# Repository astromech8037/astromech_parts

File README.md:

# Astromech Parts

This is my collection of astromechs.  
For more details on these parts, as well blueprints and general information on how to build a astromech droid, please visit https://astromech.net  

The GitHub repository will be split into the following areas:

3D Files:  This area will contain all 3D files I have created.  Each piece will have a readme with the best way to produce the file (ie:  3D printing, CNC, etc)

Electronics:  This area will contain all the electronics I have created.   In addition, any code for running the electronics will be here.

Happy building!

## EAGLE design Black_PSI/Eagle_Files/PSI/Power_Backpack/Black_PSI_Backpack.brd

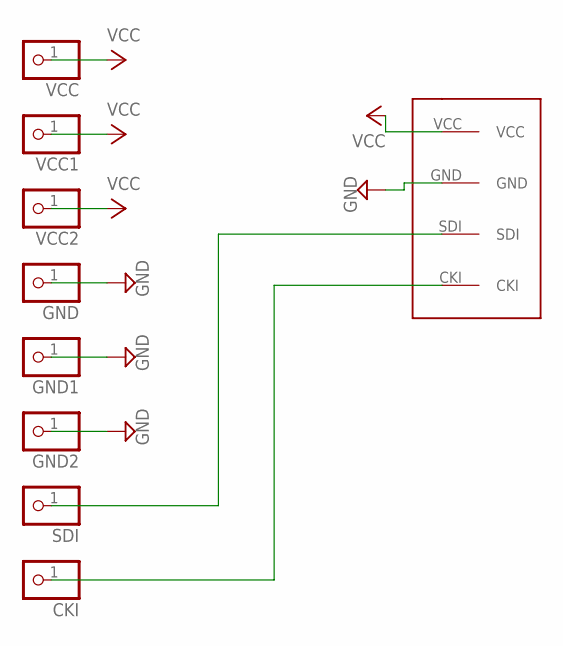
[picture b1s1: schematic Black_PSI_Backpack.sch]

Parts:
CKI: PINHD-1X1; 1X01
GND, GND1, GND2: PINHD-1X1; 1X01
SDI: PINHD-1X1; 1X01
U$1: 0393570004WIRE-TO-BOARD
VCC, VCC1, VCC2: PINHD-1X1; 1X01

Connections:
CKI: CKI.1, U$1.CKI
GND: GND.1, GND1.1, GND2.1, U$1.GND
SDI: SDI.1, U$1.SDI
VCC: U$1.VCC, VCC.1, VCC1.1, VCC2.1

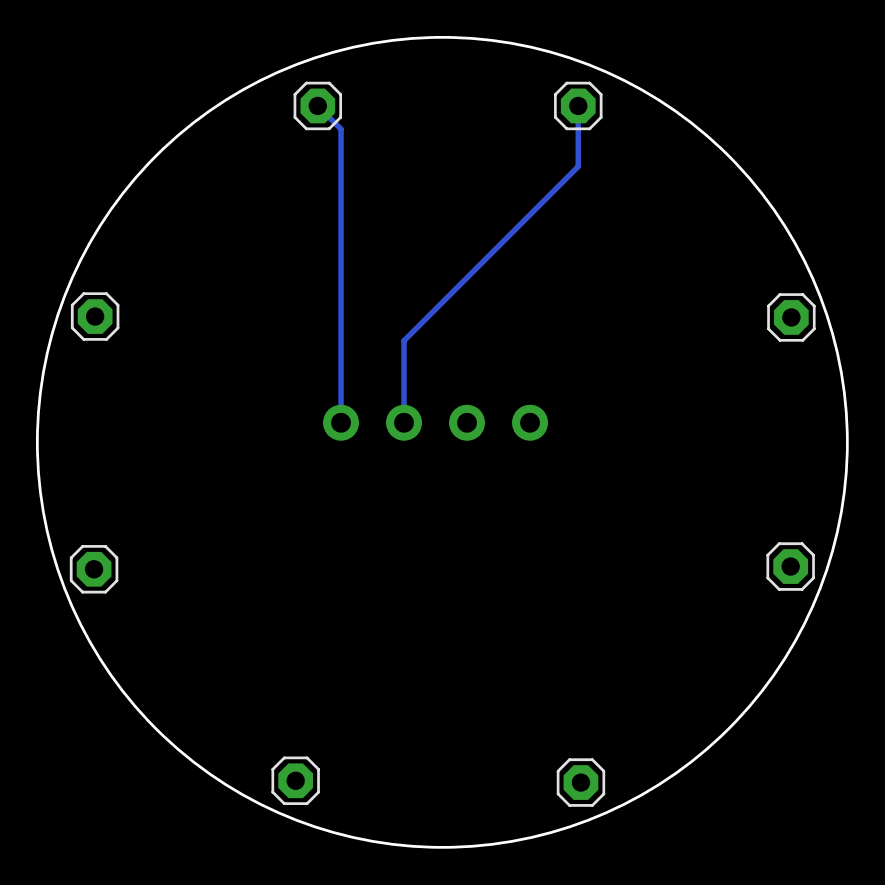
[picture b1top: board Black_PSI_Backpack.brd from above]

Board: 2 copper layers, 45.0 x 45.0 mm, 9 parts (1 on the bottom side), 4 nets.

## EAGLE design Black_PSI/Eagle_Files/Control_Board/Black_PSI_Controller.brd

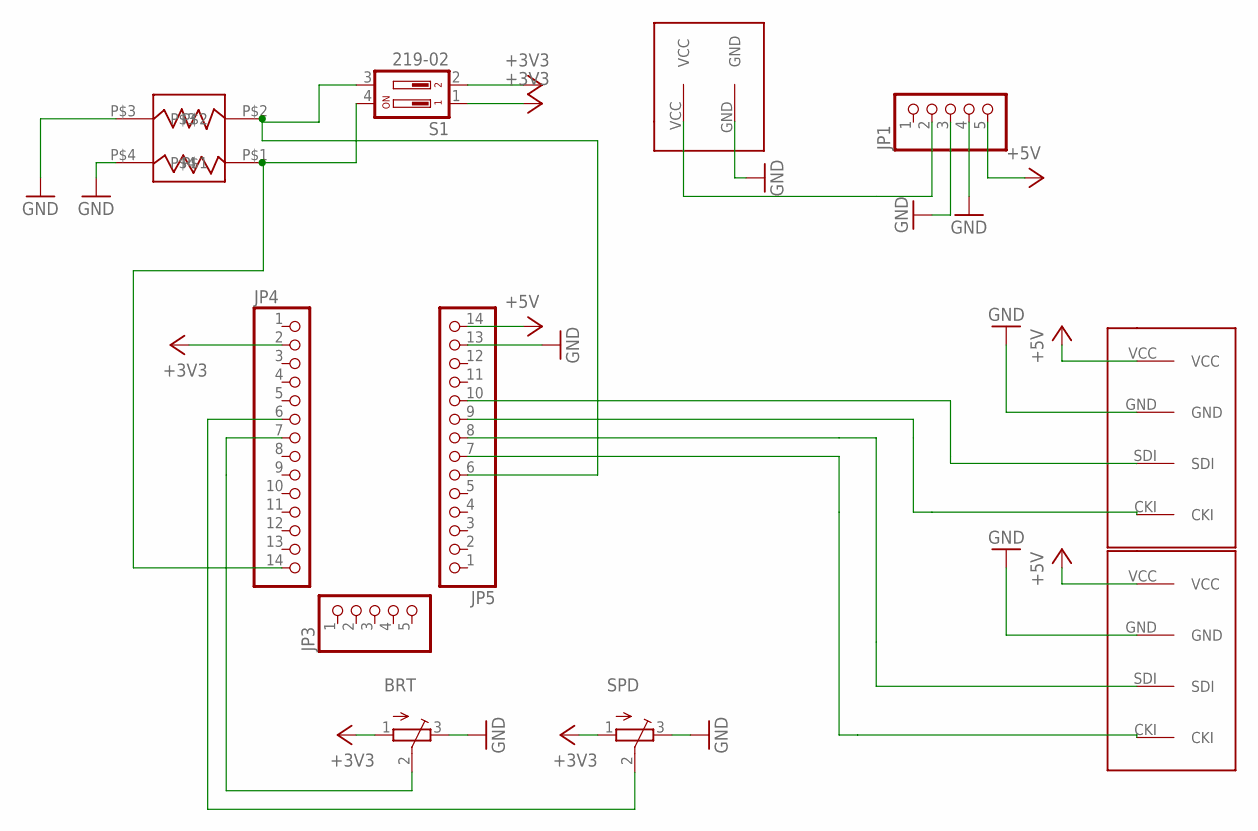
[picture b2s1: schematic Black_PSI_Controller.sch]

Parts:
BRT: TRIMPOTTC33X; TC33X
JP1, JP3: PINHD-1X5; 1X05
JP4, JP5: PINHD-1X14; 1X14
S1: 219-02; CTS-219-02
SPD: TRIMPOTTC33X; TC33X
U$1: 0393570002WIRE-TO-BOARD
U$2, U$3: 0393570004WIRE-TO-BOARD
U$4: ACASN1002S1002P1AT

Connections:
+3V3: BRT.1 (A), JP4.2, S1.1, S1.2, SPD.1 (A)
+5V: JP1.5, JP5.14, U$2.VCC, U$3.VCC
GND: BRT.3 (E), JP1.3, JP1.4, JP5.13, SPD.3 (E), U$1.GND, U$2.GND, U$3.GND, U$4.P$3, U$4.P$4
unnamed: JP4.6, SPD.2 (S)
unnamed: BRT.2 (S), JP4.7
unnamed: JP1.2, U$1.VCC
unnamed: JP5.10, U$2.SDI
unnamed: JP5.9, U$2.CKI
unnamed: JP5.8, U$3.SDI
unnamed: JP5.7, U$3.CKI
unnamed: JP4.14, S1.4, U$4.P$1
unnamed: JP5.6, S1.3, U$4.P$2

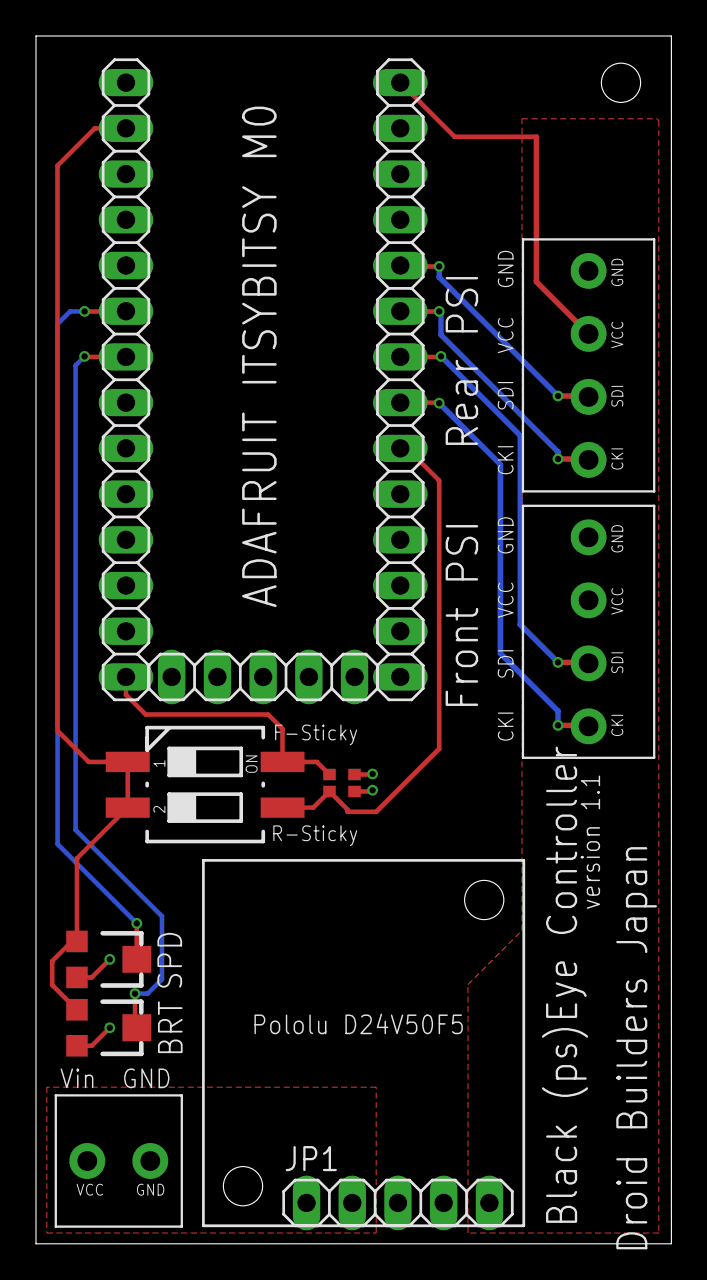
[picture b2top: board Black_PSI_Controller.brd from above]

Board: 2 copper layers, 35.3 x 67.1 mm, 11 parts (0 on the bottom side), 12 nets.

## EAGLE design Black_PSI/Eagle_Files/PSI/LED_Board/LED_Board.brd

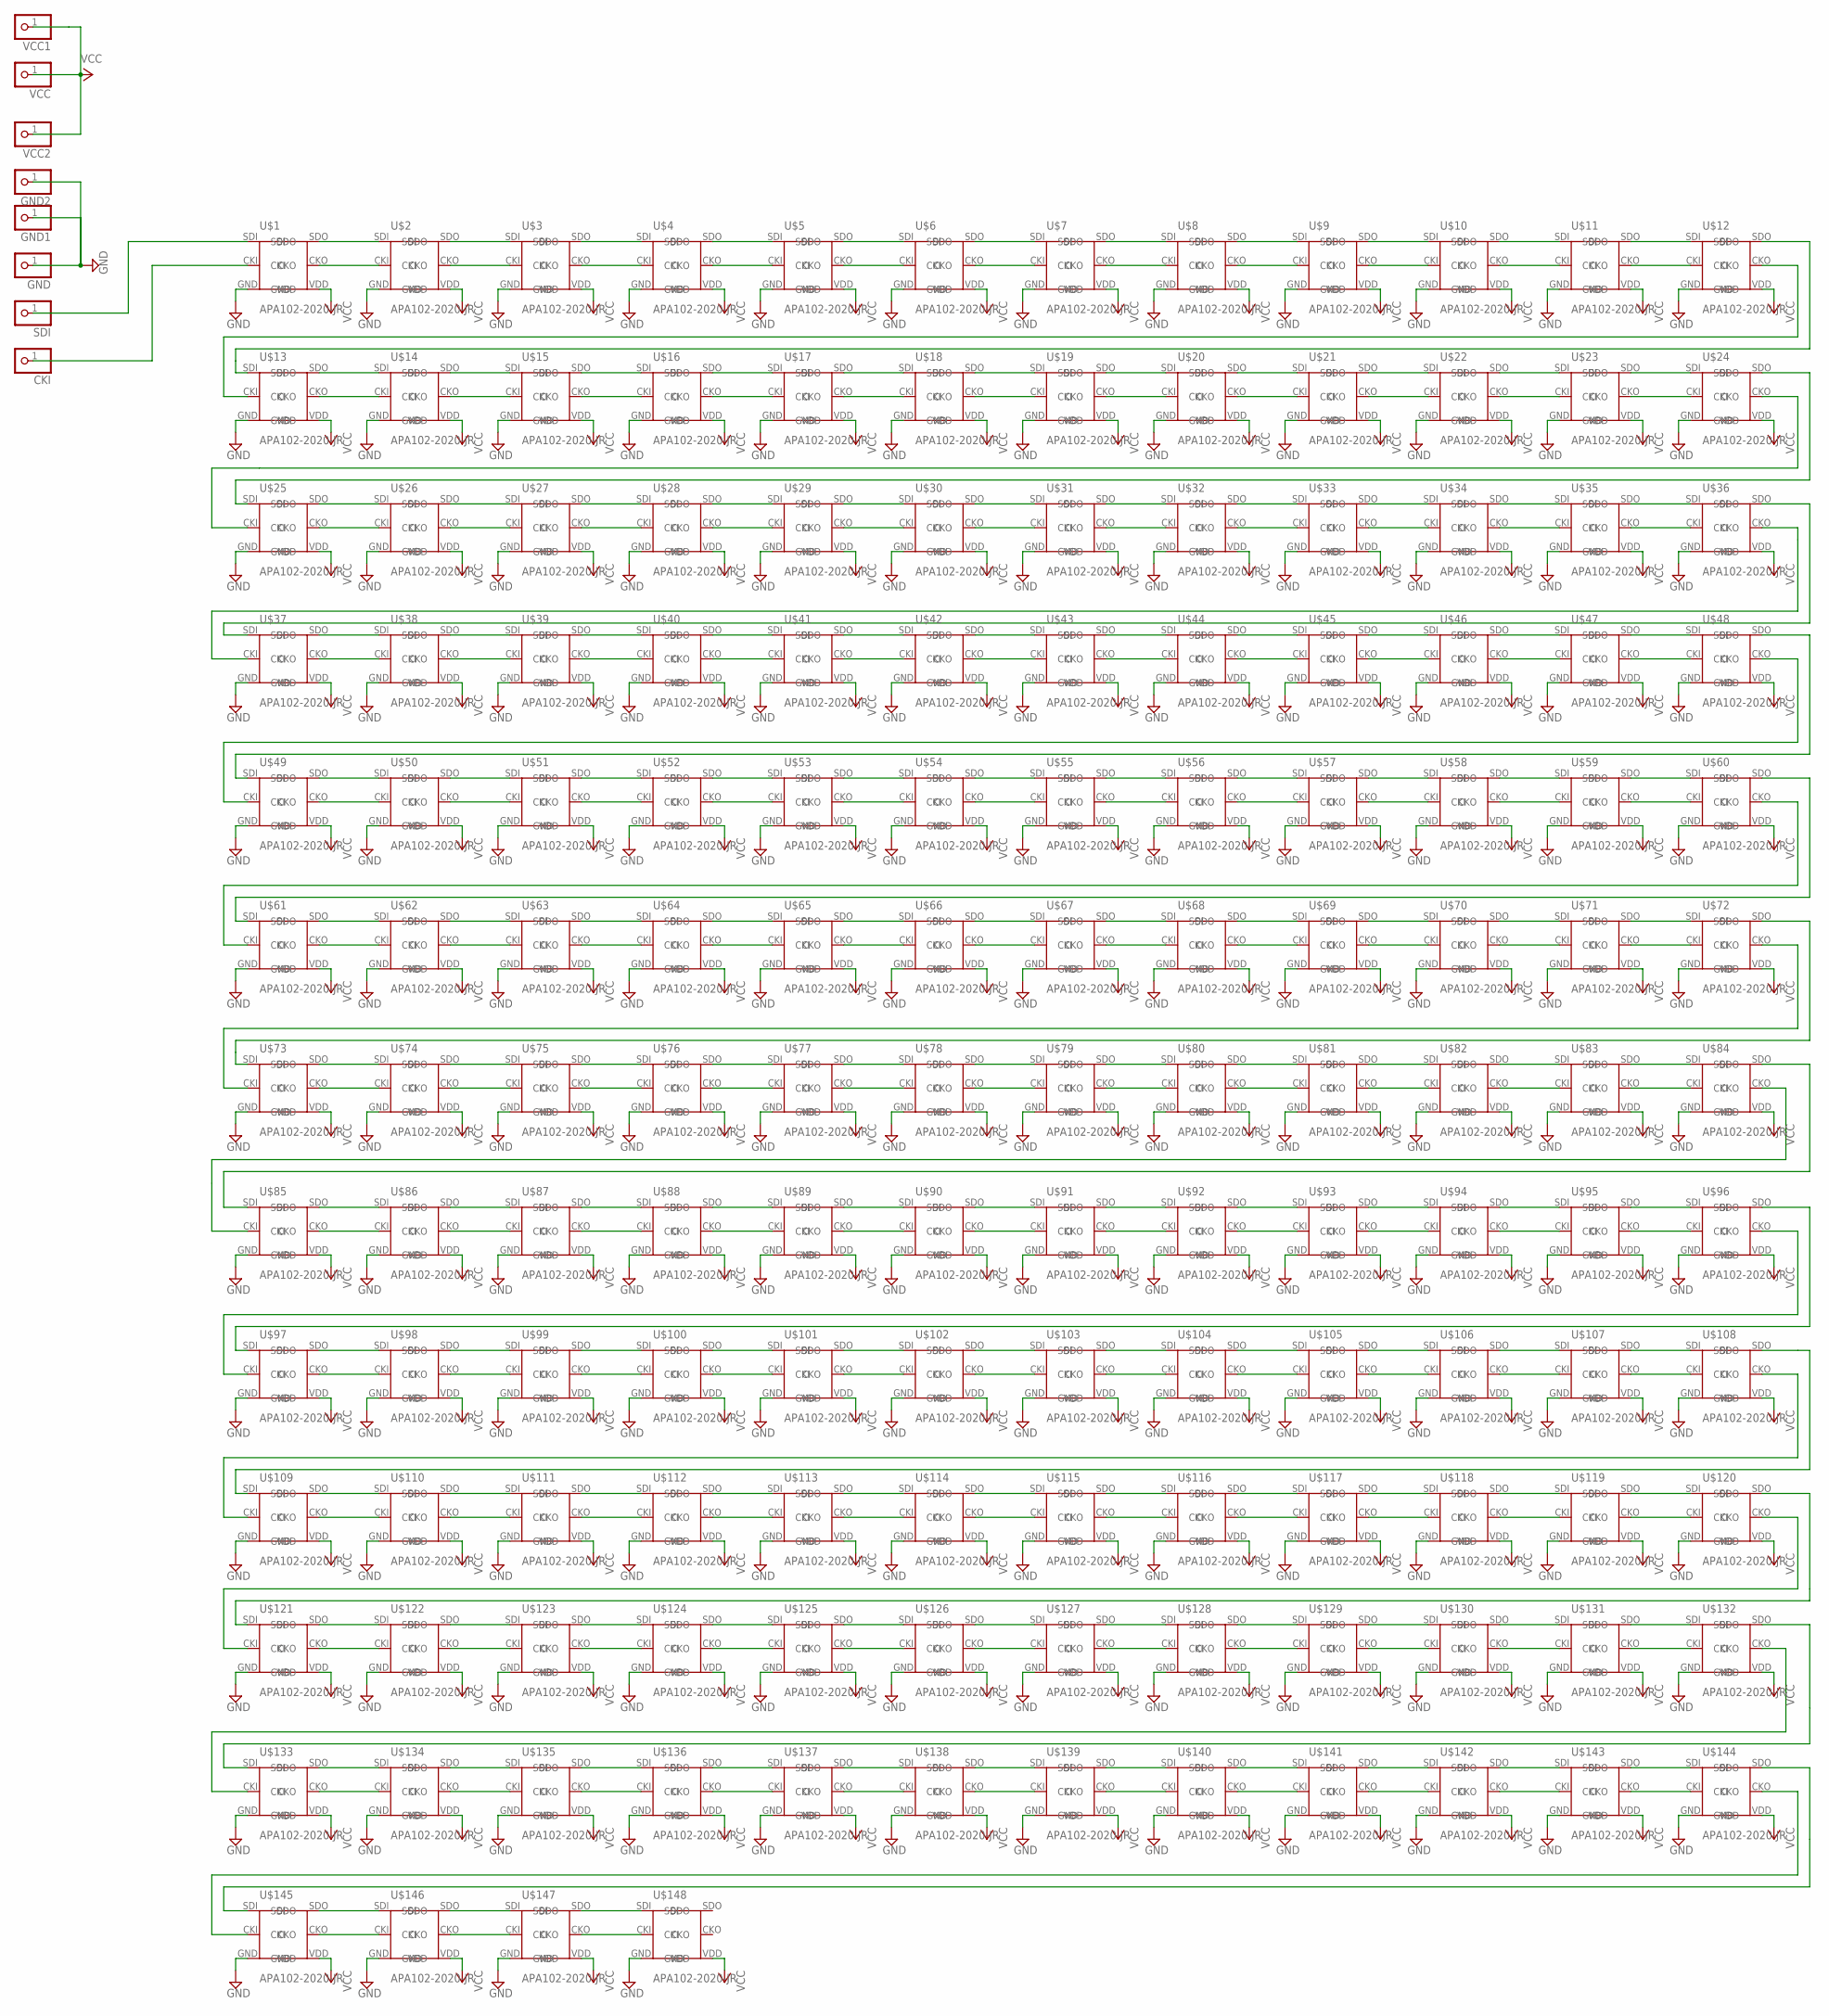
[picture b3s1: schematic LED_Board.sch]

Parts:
CKI: PINHD-1X1; 1X01
GND, GND1, GND2: PINHD-1X1; 1X01
SDI: PINHD-1X1; 1X01
U$1, U$2, U$3, U$4, U$5, U$6, U$7, U$8, U$9, U$10, U$11, U$12, U$13, U$14, U$15, U$16, U$17, U$18, U$19, U$20, U$21, U$22, U$23, U$24, U$25, U$26, U$27, U$28, U$29, U$30, U$31, U$32, U$33, U$34, U$35, U$36, U$37, U$38, U$39, U$40, U$41, U$42, U$43, U$44, U$45, U$46, U$47, U$48, U$49, U$50, U$51, U$52, U$53, U$54, U$55, U$56, U$57, U$58, U$59, U$60, U$61, U$62, U$63, U$64, U$65, U$66, U$67, U$68, U$69, U$70, U$71, U$72, U$73, U$74, U$75, U$76, U$77, U$78, U$79, U$80, U$81, U$82, U$83, U$84, U$85, U$86, U$87, U$88, U$89, U$90, U$91, U$92, U$93, U$94, U$95, U$96, U$97, U$98, U$99, U$100, U$101, U$102, U$103, U$104, U$105, U$106, U$107, U$108, U$109, U$110, U$111, U$112, U$113, U$114, U$115, U$116, U$117, U$118, U$119, U$120, U$121, U$122, U$123, U$124, U$125, U$126, U$127, U$128, U$129, U$130, U$131, U$132, U$133, U$134, U$135, U$136, U$137, U$138, U$139, U$140, U$141, U$142, U$143, U$144, U$145, U$146, U$147, U$148: APA102-2020-JR
VCC, VCC1, VCC2: PINHD-1X1; 1X01

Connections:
CK-01: U$4.CKO, U$5.CKI
CK-02: U$12.CKO, U$13.CKI
CK-03: U$22.CKO, U$23.CKI
CK-04: U$34.CKO, U$35.CKI
CK-05: U$46.CKO, U$47.CKI
CK-06: U$60.CKO, U$61.CKI
CK-07: U$74.CKO, U$75.CKI
CK-08: U$88.CKO, U$89.CKI
CK-09: U$102.CKO, U$103.CKI
CK-10: U$114.CKO, U$115.CKI
CK-11: U$126.CKO, U$127.CKI
CK-12: U$136.CKO, U$137.CKI
CK-13: U$144.CKO, U$145.CKI
GND: GND.1, GND1.1, GND2.1, U$1.GND, U$2.GND, U$3.GND, U$4.GND, U$5.GND, U$6.GND, U$7.GND, U$8.GND, U$9.GND, U$10.GND, U$11.GND, U$12.GND, U$13.GND, U$14.GND, U$15.GND, U$16.GND, U$17.GND, U$18.GND, U$19.GND, U$20.GND, U$21.GND, U$22.GND, U$23.GND, U$24.GND, U$25.GND, U$26.GND, U$27.GND, U$28.GND, U$29.GND, U$30.GND, U$31.GND, U$32.GND, U$33.GND, U$34.GND, U$35.GND, U$36.GND, U$37.GND, U$38.GND, U$39.GND, U$40.GND, U$41.GND, U$42.GND, U$43.GND, U$44.GND, U$45.GND, U$46.GND, U$47.GND, U$48.GND, U$49.GND, U$50.GND, U$51.GND, U$52.GND, U$53.GND, U$54.GND, U$55.GND, U$56.GND, U$57.GND, U$58.GND, U$59.GND, U$60.GND, U$61.GND, U$62.GND, U$63.GND, U$64.GND, U$65.GND, U$66.GND, U$67.GND, U$68.GND, U$69.GND, U$70.GND, U$71.GND, U$72.GND, U$73.GND, U$74.GND, U$75.GND, U$76.GND, U$77.GND, U$78.GND, U$79.GND, U$80.GND, U$81.GND, U$82.GND, U$83.GND, U$84.GND, U$85.GND, U$86.GND, U$87.GND, U$88.GND, U$89.GND, U$90.GND, U$91.GND, U$92.GND, U$93.GND, U$94.GND, U$95.GND, U$96.GND, U$97.GND, U$98.GND, U$99.GND, U$100.GND, U$101.GND, U$102.GND, U$103.GND, U$104.GND, U$105.GND, U$106.GND, U$107.GND, U$108.GND, U$109.GND, U$110.GND, U$111.GND, U$112.GND, U$113.GND, U$114.GND, U$115.GND, U$116.GND, U$117.GND, U$118.GND, U$119.GND, U$120.GND, U$121.GND, U$122.GND, U$123.GND, U$124.GND, U$125.GND, U$126.GND, U$127.GND, U$128.GND, U$129.GND, U$130.GND, U$131.GND, U$132.GND, U$133.GND, U$134.GND, U$135.GND, U$136.GND, U$137.GND, U$138.GND, U$139.GND, U$140.GND, U$141.GND, U$142.GND, U$143.GND, U$144.GND, U$145.GND, U$146.GND, U$147.GND, U$148.GND
unnamed: SDI.1, U$1.SDI
unnamed: CKI.1, U$1.CKI
unnamed: U$11.CKO, U$12.CKI
unnamed: U$11.SDO, U$12.SDI
unnamed: U$10.CKO, U$11.CKI
unnamed: U$10.SDO, U$11.SDI
unnamed: U$9.SDO, U$10.SDI
unnamed: U$9.CKO, U$10.CKI
unnamed: U$8.SDO, U$9.SDI
unnamed: U$8.CKO, U$9.CKI
unnamed: U$7.SDO, U$8.SDI
unnamed: U$7.CKO, U$8.CKI
unnamed: U$6.SDO, U$7.SDI
unnamed: U$6.CKO, U$7.CKI
unnamed: U$5.SDO, U$6.SDI
unnamed: U$5.CKO, U$6.CKI
unnamed: U$3.SDO, U$4.SDI
unnamed: U$3.CKO, U$4.CKI
unnamed: U$2.SDO, U$3.SDI
unnamed: U$2.CKO, U$3.CKI
unnamed: U$1.SDO, U$2.SDI
unnamed: U$1.CKO, U$2.CKI
unnamed: U$23.CKO, U$24.CKI
unnamed: U$23.SDO, U$24.SDI
unnamed: U$21.SDO, U$22.SDI
unnamed: U$21.CKO, U$22.CKI
unnamed: U$20.SDO, U$21.SDI
unnamed: U$20.CKO, U$21.CKI
unnamed: U$19.SDO, U$20.SDI
unnamed: U$19.CKO, U$20.CKI
unnamed: U$18.SDO, U$19.SDI
unnamed: U$18.CKO, U$19.CKI
unnamed: U$17.SDO, U$18.SDI
unnamed: U$17.CKO, U$18.CKI
unnamed: U$16.SDO, U$17.SDI
unnamed: U$16.CKO, U$17.CKI
unnamed: U$15.SDO, U$16.SDI
unnamed: U$15.CKO, U$16.CKI
unnamed: U$14.SDO, U$15.SDI
unnamed: U$14.CKO, U$15.CKI
unnamed: U$13.SDO, U$14.SDI
unnamed: U$13.CKO, U$14.CKI
unnamed: U$35.CKO, U$36.CKI
unnamed: U$35.SDO, U$36.SDI
unnamed: U$33.SDO, U$34.SDI
unnamed: U$33.CKO, U$34.CKI
unnamed: U$32.SDO, U$33.SDI
unnamed: U$32.CKO, U$33.CKI
unnamed: U$31.SDO, U$32.SDI
unnamed: U$31.CKO, U$32.CKI
unnamed: U$30.SDO, U$31.SDI
unnamed: U$30.CKO, U$31.CKI
unnamed: U$29.SDO, U$30.SDI
unnamed: U$29.CKO, U$30.CKI
unnamed: U$28.SDO, U$29.SDI
unnamed: U$28.CKO, U$29.CKI
unnamed: U$27.SDO, U$28.SDI
unnamed: U$27.CKO, U$28.CKI
unnamed: U$26.SDO, U$27.SDI
unnamed: U$26.CKO, U$27.CKI
unnamed: U$25.SDO, U$26.SDI
unnamed: U$25.CKO, U$26.CKI
unnamed: U$47.CKO, U$48.CKI
unnamed: U$47.SDO, U$48.SDI
unnamed: U$45.SDO, U$46.SDI
unnamed: U$45.CKO, U$46.CKI
unnamed: U$44.SDO, U$45.SDI
unnamed: U$44.CKO, U$45.CKI
unnamed: U$43.SDO, U$44.SDI
unnamed: U$43.CKO, U$44.CKI
unnamed: U$42.SDO, U$43.SDI
unnamed: U$42.CKO, U$43.CKI
unnamed: U$41.SDO, U$42.SDI
unnamed: U$41.CKO, U$42.CKI
unnamed: U$40.SDO, U$41.SDI
unnamed: U$40.CKO, U$41.CKI
unnamed: U$39.SDO, U$40.SDI
unnamed: U$39.CKO, U$40.CKI
unnamed: U$38.SDO, U$39.SDI
unnamed: U$38.CKO, U$39.CKI
unnamed: U$37.SDO, U$38.SDI
unnamed: U$37.CKO, U$38.CKI
unnamed: U$59.CKO, U$60.CKI
unnamed: U$59.SDO, U$60.SDI
unnamed: U$58.CKO, U$59.CKI
unnamed: U$58.SDO, U$59.SDI
unnamed: U$57.SDO, U$58.SDI
unnamed: U$57.CKO, U$58.CKI
unnamed: U$56.SDO, U$57.SDI
unnamed: U$56.CKO, U$57.CKI
unnamed: U$55.SDO, U$56.SDI
unnamed: U$55.CKO, U$56.CKI
unnamed: U$54.SDO, U$55.SDI
unnamed: U$54.CKO, U$55.CKI
unnamed: U$53.SDO, U$54.SDI
unnamed: U$53.CKO, U$54.CKI
unnamed: U$52.SDO, U$53.SDI
unnamed: U$52.CKO, U$53.CKI
unnamed: U$51.SDO, U$52.SDI
unnamed: U$51.CKO, U$52.CKI
unnamed: U$50.SDO, U$51.SDI
unnamed: U$50.CKO, U$51.CKI
unnamed: U$49.SDO, U$50.SDI
unnamed: U$49.CKO, U$50.CKI
unnamed: U$71.CKO, U$72.CKI
unnamed: U$71.SDO, U$72.SDI
unnamed: U$70.CKO, U$71.CKI
unnamed: U$70.SDO, U$71.SDI
unnamed: U$69.SDO, U$70.SDI
unnamed: U$69.CKO, U$70.CKI
unnamed: U$68.SDO, U$69.SDI
unnamed: U$68.CKO, U$69.CKI
unnamed: U$67.SDO, U$68.SDI
unnamed: U$67.CKO, U$68.CKI
unnamed: U$66.SDO, U$67.SDI
unnamed: U$66.CKO, U$67.CKI
unnamed: U$65.SDO, U$66.SDI
unnamed: U$65.CKO, U$66.CKI
unnamed: U$64.SDO, U$65.SDI
unnamed: U$64.CKO, U$65.CKI
unnamed: U$63.SDO, U$64.SDI
unnamed: U$63.CKO, U$64.CKI
unnamed: U$62.SDO, U$63.SDI
unnamed: U$62.CKO, U$63.CKI
unnamed: U$61.SDO, U$62.SDI
unnamed: U$61.CKO, U$62.CKI
unnamed: U$83.CKO, U$84.CKI
unnamed: U$83.SDO, U$84.SDI
unnamed: U$82.CKO, U$83.CKI
unnamed: U$82.SDO, U$83.SDI
unnamed: U$81.SDO, U$82.SDI
unnamed: U$81.CKO, U$82.CKI
unnamed: U$80.SDO, U$81.SDI
unnamed: U$80.CKO, U$81.CKI
unnamed: U$79.SDO, U$80.SDI
unnamed: U$79.CKO, U$80.CKI
unnamed: U$78.SDO, U$79.SDI
unnamed: U$78.CKO, U$79.CKI
unnamed: U$77.SDO, U$78.SDI
unnamed: U$77.CKO, U$78.CKI
unnamed: U$76.SDO, U$77.SDI
unnamed: U$76.CKO, U$77.CKI
unnamed: U$75.SDO, U$76.SDI
unnamed: U$75.CKO, U$76.CKI
unnamed: U$73.SDO, U$74.SDI
unnamed: U$73.CKO, U$74.CKI
unnamed: U$95.CKO, U$96.CKI
unnamed: U$95.SDO, U$96.SDI
unnamed: U$94.CKO, U$95.CKI
unnamed: U$94.SDO, U$95.SDI
unnamed: U$93.SDO, U$94.SDI
unnamed: U$93.CKO, U$94.CKI
unnamed: U$92.SDO, U$93.SDI
unnamed: U$92.CKO, U$93.CKI
unnamed: U$91.SDO, U$92.SDI
unnamed: U$91.CKO, U$92.CKI
unnamed: U$90.SDO, U$91.SDI
unnamed: U$90.CKO, U$91.CKI
unnamed: U$89.SDO, U$90.SDI
unnamed: U$89.CKO, U$90.CKI
unnamed: U$87.SDO, U$88.SDI
unnamed: U$87.CKO, U$88.CKI
unnamed: U$86.SDO, U$87.SDI
unnamed: U$86.CKO, U$87.CKI
unnamed: U$85.SDO, U$86.SDI
unnamed: U$85.CKO, U$86.CKI
unnamed: U$107.CKO, U$108.CKI
unnamed: U$107.SDO, U$108.SDI
unnamed: U$106.CKO, U$107.CKI
unnamed: U$106.SDO, U$107.SDI
unnamed: U$105.SDO, U$106.SDI
unnamed: U$105.CKO, U$106.CKI
unnamed: U$104.SDO, U$105.SDI
unnamed: U$104.CKO, U$105.CKI
unnamed: U$103.SDO, U$104.SDI
unnamed: U$103.CKO, U$104.CKI
unnamed: U$101.SDO, U$102.SDI
unnamed: U$101.CKO, U$102.CKI
unnamed: U$100.SDO, U$101.SDI
unnamed: U$100.CKO, U$101.CKI
unnamed: U$99.SDO, U$100.SDI
unnamed: U$99.CKO, U$100.CKI
unnamed: U$98.SDO, U$99.SDI
unnamed: U$98.CKO, U$99.CKI
unnamed: U$97.SDO, U$98.SDI
unnamed: U$97.CKO, U$98.CKI
unnamed: U$119.CKO, U$120.CKI
unnamed: U$119.SDO, U$120.SDI
unnamed: U$118.CKO, U$119.CKI
unnamed: U$118.SDO, U$119.SDI
unnamed: U$117.SDO, U$118.SDI
unnamed: U$117.CKO, U$118.CKI
unnamed: U$116.SDO, U$117.SDI
unnamed: U$116.CKO, U$117.CKI
unnamed: U$115.SDO, U$116.SDI
unnamed: U$115.CKO, U$116.CKI
unnamed: U$113.SDO, U$114.SDI
unnamed: U$113.CKO, U$114.CKI
unnamed: U$112.SDO, U$113.SDI
unnamed: U$112.CKO, U$113.CKI
unnamed: U$111.SDO, U$112.SDI
unnamed: U$111.CKO, U$112.CKI
unnamed: U$110.SDO, U$111.SDI
unnamed: U$110.CKO, U$111.CKI
unnamed: U$109.SDO, U$110.SDI
unnamed: U$109.CKO, U$110.CKI
unnamed: U$131.CKO, U$132.CKI
unnamed: U$131.SDO, U$132.SDI
unnamed: U$130.CKO, U$131.CKI
unnamed: U$130.SDO, U$131.SDI
unnamed: U$129.SDO, U$130.SDI
unnamed: U$129.CKO, U$130.CKI
unnamed: U$128.SDO, U$129.SDI
unnamed: U$128.CKO, U$129.CKI
unnamed: U$127.SDO, U$128.SDI
unnamed: U$127.CKO, U$128.CKI
unnamed: U$125.SDO, U$126.SDI
unnamed: U$125.CKO, U$126.CKI
unnamed: U$124.SDO, U$125.SDI
unnamed: U$124.CKO, U$125.CKI
unnamed: U$123.SDO, U$124.SDI
unnamed: U$123.CKO, U$124.CKI
unnamed: U$122.SDO, U$123.SDI
unnamed: U$122.CKO, U$123.CKI
unnamed: U$121.SDO, U$122.SDI
unnamed: U$121.CKO, U$122.CKI
unnamed: U$143.CKO, U$144.CKI
unnamed: U$143.SDO, U$144.SDI
unnamed: U$142.CKO, U$143.CKI
unnamed: U$142.SDO, U$143.SDI
unnamed: U$141.SDO, U$142.SDI
unnamed: U$141.CKO, U$142.CKI
unnamed: U$140.SDO, U$141.SDI
unnamed: U$140.CKO, U$141.CKI
unnamed: U$139.SDO, U$140.SDI
unnamed: U$139.CKO, U$140.CKI
unnamed: U$138.SDO, U$139.SDI
unnamed: U$138.CKO, U$139.CKI
unnamed: U$137.SDO, U$138.SDI
unnamed: U$137.CKO, U$138.CKI
unnamed: U$135.SDO, U$136.SDI
unnamed: U$135.CKO, U$136.CKI
unnamed: U$134.SDO, U$135.SDI
unnamed: U$134.CKO, U$135.CKI
unnamed: U$133.SDO, U$134.SDI
unnamed: U$133.CKO, U$134.CKI
unnamed: U$24.SDO, U$25.SDI
unnamed: U$24.CKO, U$25.CKI
unnamed: U$36.SDO, U$37.SDI
unnamed: U$36.CKO, U$37.CKI
unnamed: U$48.SDO, U$49.SDI
unnamed: U$48.CKO, U$49.CKI
unnamed: U$72.SDO, U$73.SDI
unnamed: U$72.CKO, U$73.CKI
unnamed: U$84.SDO, U$85.SDI
unnamed: U$84.CKO, U$85.CKI
unnamed: U$96.SDO, U$97.SDI
unnamed: U$96.CKO, U$97.CKI
unnamed: U$147.SDO, U$148.SDI
unnamed: U$147.CKO, U$148.CKI
unnamed: U$146.SDO, U$147.SDI
unnamed: U$146.CKO, U$147.CKI
unnamed: U$145.SDO, U$146.SDI
unnamed: U$145.CKO, U$146.CKI
unnamed: U$108.SDO, U$109.SDI
unnamed: U$108.CKO, U$109.CKI
unnamed: U$120.SDO, U$121.SDI
unnamed: U$120.CKO, U$121.CKI
unnamed: U$132.SDO, U$133.SDI
unnamed: U$132.CKO, U$133.CKI
SD-01: U$4.SDO, U$5.SDI
SD-02: U$12.SDO, U$13.SDI
SD-03: U$22.SDO, U$23.SDI
SD-04: U$34.SDO, U$35.SDI
SD-05: U$46.SDO, U$47.SDI
SD-06: U$60.SDO, U$61.SDI
SD-07: U$74.SDO, U$75.SDI
SD-08: U$88.SDO, U$89.SDI
SD-09: U$102.SDO, U$103.SDI
SD-10: U$114.SDO, U$115.SDI
SD-11: U$126.SDO, U$127.SDI
SD-12: U$136.SDO, U$137.SDI
SD-13: U$144.SDO, U$145.SDI
VCC: U$1.VDD, U$2.VDD, U$3.VDD, U$4.VDD, U$5.VDD, U$6.VDD, U$7.VDD, U$8.VDD, U$9.VDD, U$10.VDD, U$11.VDD, U$12.VDD, U$13.VDD, U$14.VDD, U$15.VDD, U$16.VDD, U$17.VDD, U$18.VDD, U$19.VDD, U$20.VDD, U$21.VDD, U$22.VDD, U$23.VDD, U$24.VDD, U$25.VDD, U$26.VDD, U$27.VDD, U$28.VDD, U$29.VDD, U$30.VDD, U$31.VDD, U$32.VDD, U$33.VDD, U$34.VDD, U$35.VDD, U$36.VDD, U$37.VDD, U$38.VDD, U$39.VDD, U$40.VDD, U$41.VDD, U$42.VDD, U$43.VDD, U$44.VDD, U$45.VDD, U$46.VDD, U$47.VDD, U$48.VDD, U$49.VDD, U$50.VDD, U$51.VDD, U$52.VDD, U$53.VDD, U$54.VDD, U$55.VDD, U$56.VDD, U$57.VDD, U$58.VDD, U$59.VDD, U$60.VDD, U$61.VDD, U$62.VDD, U$63.VDD, U$64.VDD, U$65.VDD, U$66.VDD, U$67.VDD, U$68.VDD, U$69.VDD, U$70.VDD, U$71.VDD, U$72.VDD, U$73.VDD, U$74.VDD, U$75.VDD, U$76.VDD, U$77.VDD, U$78.VDD, U$79.VDD, U$80.VDD, U$81.VDD, U$82.VDD, U$83.VDD, U$84.VDD, U$85.VDD, U$86.VDD, U$87.VDD, U$88.VDD, U$89.VDD, U$90.VDD, U$91.VDD, U$92.VDD, U$93.VDD, U$94.VDD, U$95.VDD, U$96.VDD, U$97.VDD, U$98.VDD, U$99.VDD, U$100.VDD, U$101.VDD, U$102.VDD, U$103.VDD, U$104.VDD, U$105.VDD, U$106.VDD, U$107.VDD, U$108.VDD, U$109.VDD, U$110.VDD, U$111.VDD, U$112.VDD, U$113.VDD, U$114.VDD, U$115.VDD, U$116.VDD, U$117.VDD, U$118.VDD, U$119.VDD, U$120.VDD, U$121.VDD, U$122.VDD, U$123.VDD, U$124.VDD, U$125.VDD, U$126.VDD, U$127.VDD, U$128.VDD, U$129.VDD, U$130.VDD, U$131.VDD, U$132.VDD, U$133.VDD, U$134.VDD, U$135.VDD, U$136.VDD, U$137.VDD, U$138.VDD, U$139.VDD, U$140.VDD, U$141.VDD, U$142.VDD, U$143.VDD, U$144.VDD, U$145.VDD, U$146.VDD, U$147.VDD, U$148.VDD, VCC.1, VCC1.1, VCC2.1

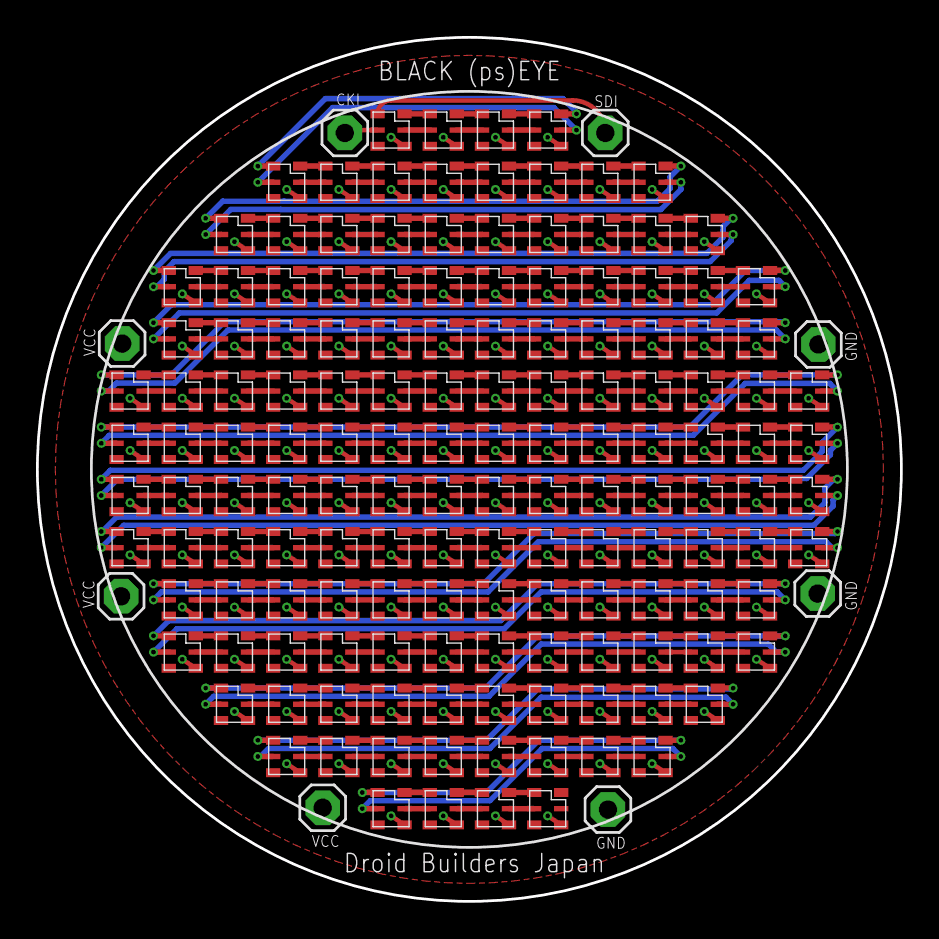
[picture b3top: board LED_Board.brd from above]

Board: 2 copper layers, 48.0 x 48.0 mm, 156 parts (0 on the bottom side), 298 nets.

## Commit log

2019-03-10 BOM - Build of Materials
    A list of all items needed for 1 complete set of PSI lights for an R2 unit.
